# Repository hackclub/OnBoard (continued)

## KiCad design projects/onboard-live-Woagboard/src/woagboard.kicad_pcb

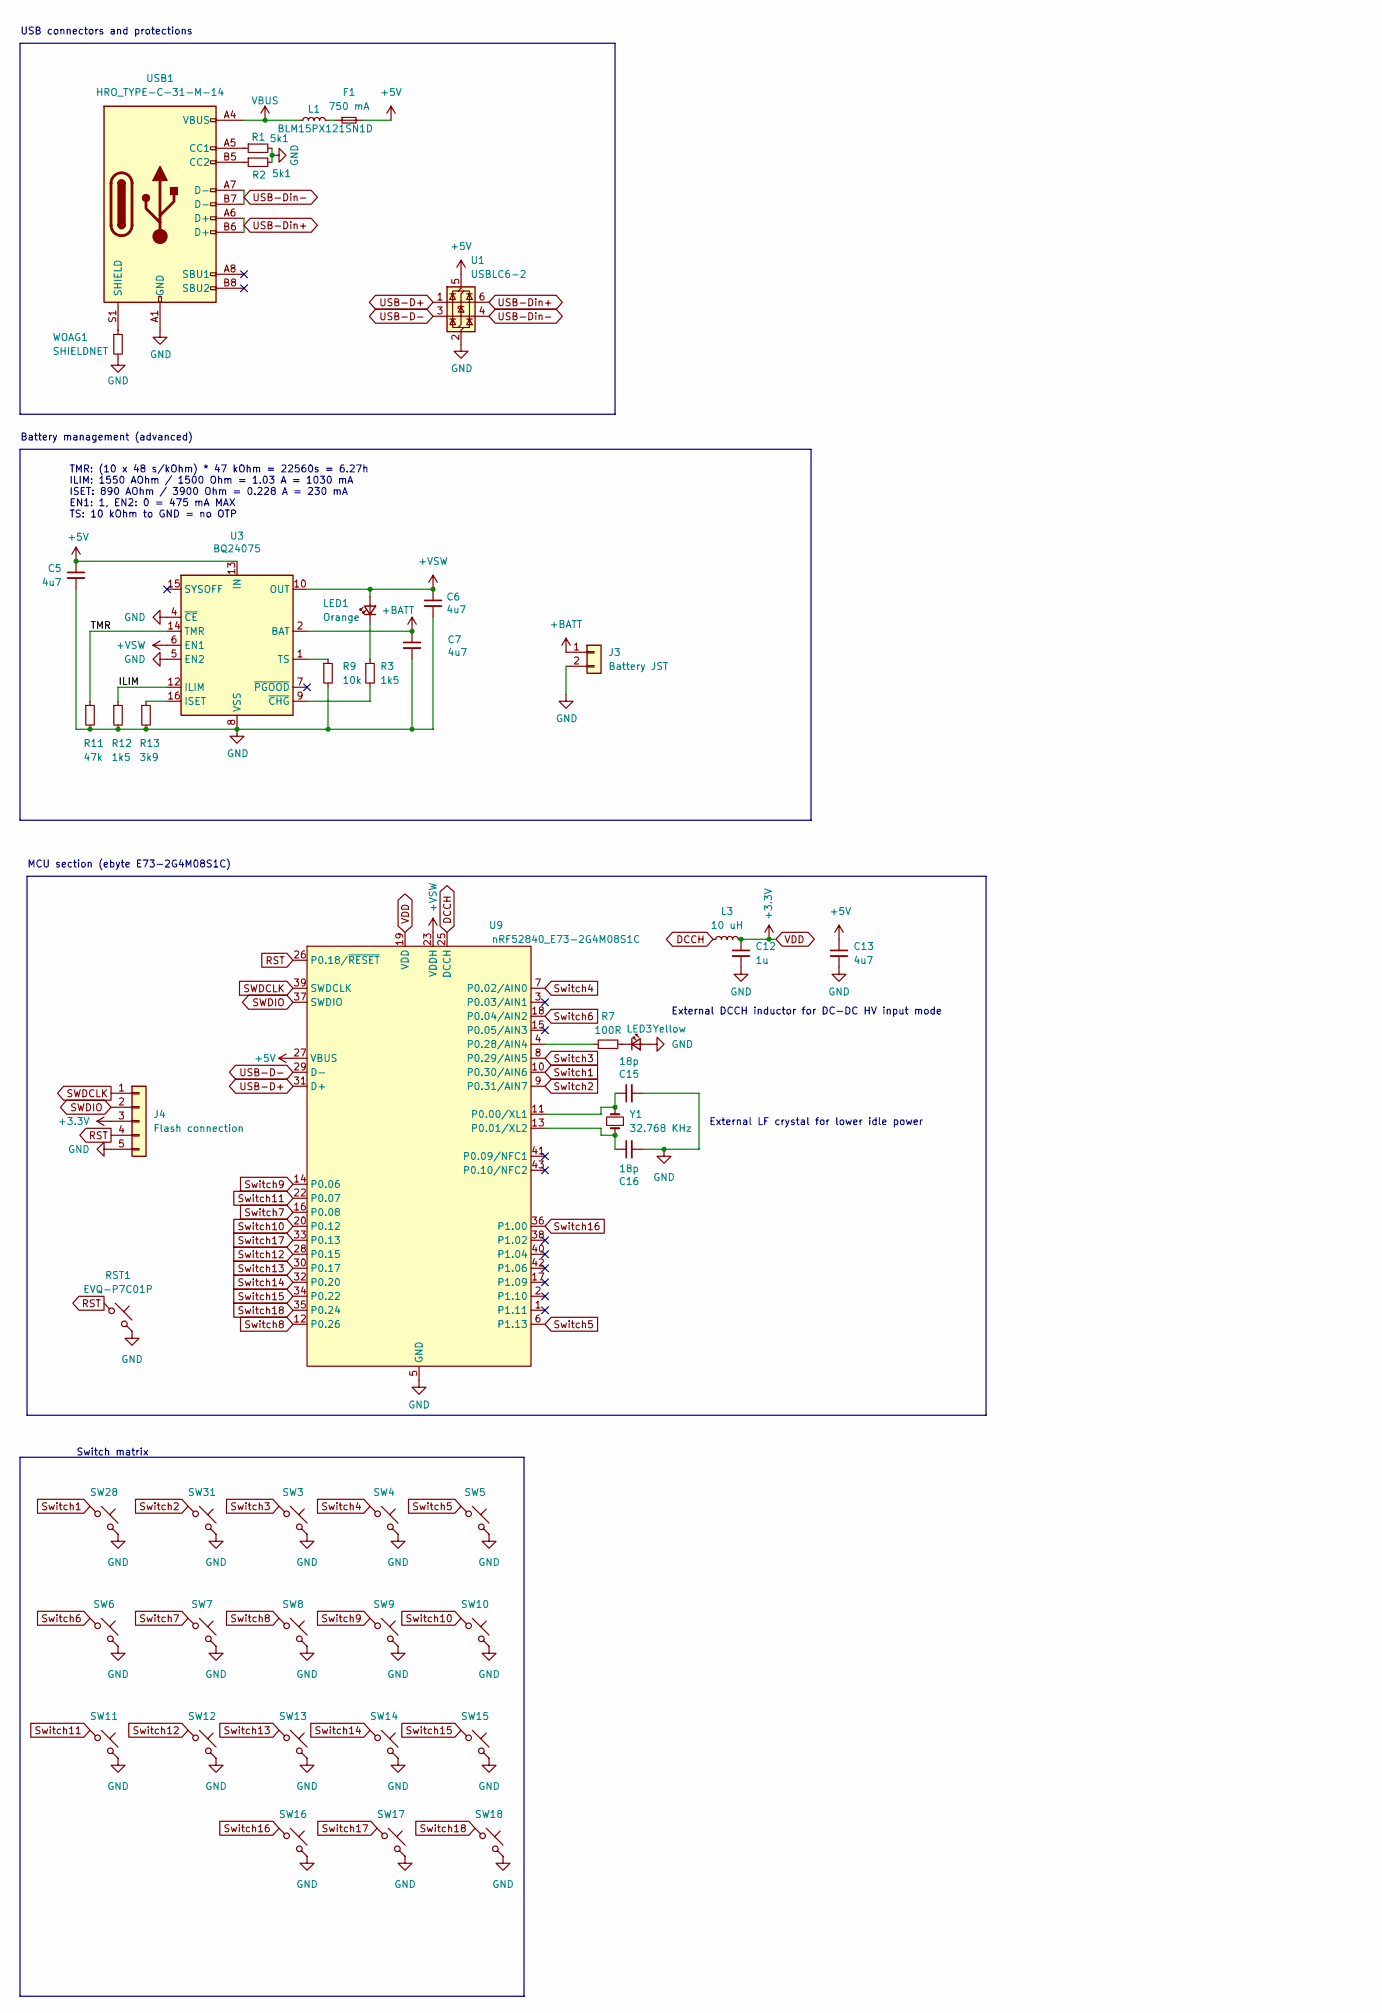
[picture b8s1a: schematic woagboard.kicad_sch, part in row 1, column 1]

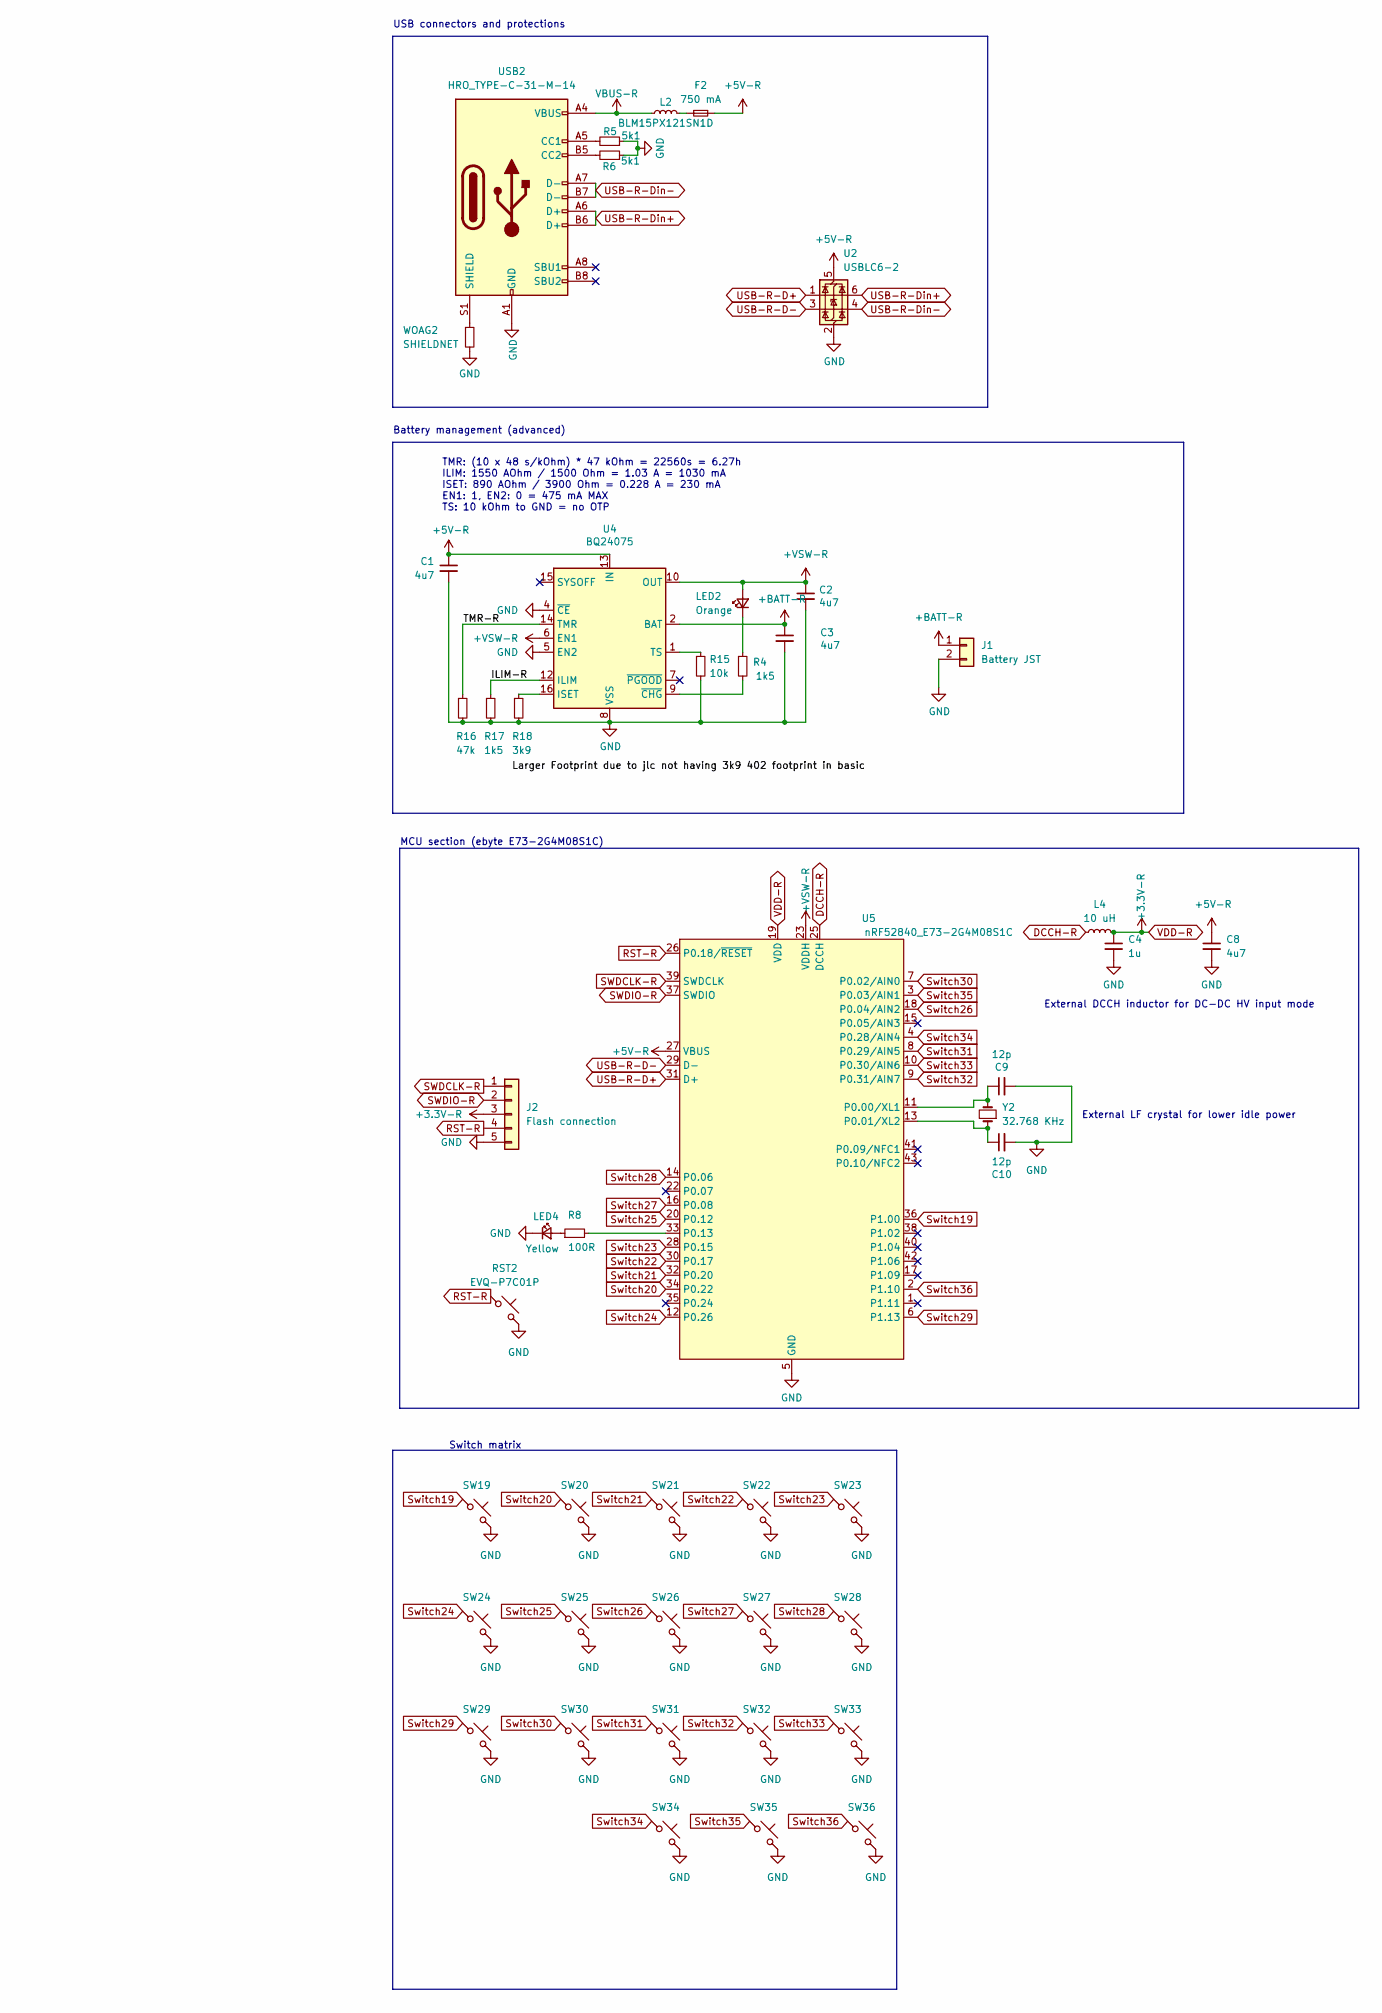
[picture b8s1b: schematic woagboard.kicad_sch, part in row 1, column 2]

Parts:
C1, C2, C3, C5, C6, C7, C8, C13: 4u7; C_0402_1005Metric
C4, C12: 1u; C_0402_1005Metric
C9, C10: 12p; C_0402_1005Metric
C15, C16: 18p; C_0402_1005Metric
F1, F2: 750 mA; Fuse_0603_1608Metric
J1, J3: Battery JST; JST_PH_S2B-PH-K_1x02_P2.00mm_Horizontal
J2, J4: Flash connection; PinHeader_1x05_P2.54mm_Vertical
L1, L2: BLM15PX121SN1D; L_0402_1005Metric
L3, L4: 10 uH; L_0603_1608Metric; LCSC C92982
LED1, LED2: Orange; LED_0805_2012Metric
LED3, LED4: Yellow; LED_0805_2012Metric
R1, R2, R5, R6: 5k1; R_0402_1005Metric
R3, R4, R12, R17: 1k5; R_0402_1005Metric
R7, R8: 100R; R_0402_1005Metric
R9, R15: 10k; R_0402_1005Metric
R11, R16: 47k; R_0402_1005Metric
R13, R18: 3k9; R_0603_1608Metric
RST1, RST2: EVQ-P7C01P; EVQ-P7C
SW3, SW4, SW5, SW6, SW7, SW8, SW9, SW10, SW11, SW12, SW13, SW14, SW15, SW16, SW17, SW18, SW19, SW20, SW21, SW22, SW23, SW24, SW25, SW26, SW27, SW28, SW29, SW30, SW31, SW32, SW33, SW34, SW35, SW36: SW_Push; SW_choc_v1_HS_No_LED
U1, U2: USBLC6-2; SOT-23-6
U3, U4: BQ24075; VQFN-16-1EP_3x3mm_P0.5mm_EP1.68x1.68mm
U5, U9: nRF52840_E73-2G4M08S1C; LCSC C356849
USB1, USB2: HRO_TYPE-C-31-M-14; USB_C_Receptacle_HRO_TYPE-C-31-M-12
WOAG1, WOAG2: SHIELDNET; SolderJumper-2_P1.3mm_Bridged2Bar_RoundedPad1.0x1.5mm
Y1, Y2: 32.768 KHz; Q13FC13500004; LCSC C55208

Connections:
+5V: C5.1, C13.1, F1.2, U1.5 (VBUS), U3.13 (IN), U9.27 (VBUS)
+5V-R: C1.1, C8.1, F2.2, U2.5 (VBUS), U4.13 (IN), U5.27 (VBUS)
+BATT: C7.1, J3.1, U3.2 (BAT), U3.3 (BAT)
+BATT-R: C3.1, J1.1, U4.2 (BAT), U4.3 (BAT)
+VSW: C6.1, LED1.2 (A), U3.6 (EN1), U3.10 (OUT), U3.11 (OUT), U9.23 (VDDH)
+VSW-R: C2.1, LED2.2 (A), U4.6 (EN1), U4.10 (OUT), U4.11 (OUT), U5.23 (VDDH)
/ILIM: R12.1, U3.12 (ILIM)
/ILIM-R: R17.1, U4.12 (ILIM)
/TMR: R11.1, U3.14 (TMR)
/TMR-R: R16.1, U4.14 (TMR)
DCCH: L3.1, U9.25 (DCCH)
DCCH-R: L4.1, U5.25 (DCCH)
GND: C1.2, C2.2, C3.2, C4.2, C5.2, C6.2, C7.2, C8.2, C9.2, C10.2, C12.2, C13.2, C15.2, C16.2, J1.2, J2.5, J3.2, J4.5, LED3.2 (A), LED4.1 (K), R1.2, R2.2, R5.1, R6.1, R9.2, R11.2, R12.2, R13.2, R15.2, R16.2, R17.2, R18.2, RST1.2, RST2.2, SW3.2, SW4.2, SW5.2, SW6.2, SW7.2, SW8.2, SW9.2, SW10.2, SW11.2, SW12.2, SW13.2, SW14.2, SW15.2, SW16.2, SW17.2, SW18.2, SW19.2, SW20.2, SW21.2, SW22.2, SW23.2, SW24.2, SW25.2, SW26.2, SW27.2, SW28.2, SW29.2, SW30.2, SW31.2, SW32.2, SW33.2, SW34.2, SW35.2, SW36.2, U1.2 (GND), U2.2 (GND), U3.4 (~CE), U3.5 (EN2), U3.8 (VSS), U3.17 (VSS), U4.4 (~CE), U4.5 (EN2), U4.8 (VSS), U4.17 (VSS), U5.5 (GND), U5.21 (GND), U5.24 (GND), U9.5 (GND), U9.21 (GND), U9.24 (GND), USB1.A1 (GND), USB1.A12 (GND), USB1.B1 (GND), USB1.B12 (GND), USB2.A1 (GND), USB2.A12 (GND), USB2.B1 (GND), USB2.B12 (GND), WOAG1.2, WOAG2.2; also elsewhere on the board
unnamed: F1.1, L1.2
unnamed: F2.1, L2.2
unnamed: LED1.1 (K), R3.1
unnamed: LED2.1 (K), R4.1
unnamed: LED3.1 (K), R7.2
unnamed: LED4.2 (A), R8.1
unnamed: R13.1, U3.16 (ISET)
unnamed: R9.1, U3.1 (TS)
unnamed: R3.2, U3.9 (~CHG)
unnamed: R18.1, U4.16 (ISET)
unnamed: R15.1, U4.1 (TS)
unnamed: R4.2, U4.9 (~CHG)
unnamed: C9.1, U5.11 (P0.00/XL1), Y2.2
unnamed: C10.1, U5.13 (P0.01/XL2), Y2.1
unnamed: R8.2, U5.33 (P0.13)
unnamed: C15.1, U9.11 (P0.00/XL1), Y1.2
unnamed: C16.1, U9.13 (P0.01/XL2), Y1.1
unnamed: R7.1, U9.4 (P0.28/AIN4)
unnamed: R1.1, USB1.A5 (CC1)
unnamed: R2.1, USB1.B5 (CC2)
unnamed: USB1.S1 (SHIELD), WOAG1.1
unnamed: R5.2, USB2.A5 (CC1)
unnamed: R6.2, USB2.B5 (CC2)
unnamed: USB2.S1 (SHIELD), WOAG2.1
RST: J4.4, RST1.1, U9.26 (P0.18/~RESET)
RST-R: J2.4, RST2.1, U5.26 (P0.18/~RESET)
SWDCLK: J4.1, U9.39 (SWDCLK)
SWDCLK-R: J2.1, U5.39 (SWDCLK)
SWDIO: J4.2, U9.37 (SWDIO)
SWDIO-R: J2.2, U5.37 (SWDIO)
Switch3: SW3.1, U9.8 (P0.29/AIN5)
Switch4: SW4.1, U9.7 (P0.02/AIN0)
Switch5: SW5.1, U9.6 (P1.13)
Switch6: SW6.1, U9.18 (P0.04/AIN2)
Switch7: SW7.1, U9.16 (P0.08)
Switch8: SW8.1, U9.12 (P0.26)
Switch9: SW9.1, U9.14 (P0.06)
Switch10: SW10.1, U9.20 (P0.12)
Switch11: SW11.1, U9.22 (P0.07)
Switch12: SW12.1, U9.28 (P0.15)
Switch13: SW13.1, U9.30 (P0.17)
Switch14: SW14.1, U9.32 (P0.20)
Switch15: SW15.1, U9.34 (P0.22)
Switch16: SW16.1, U9.36 (P1.00)
Switch17: SW17.1, U9.33 (P0.13)
Switch18: SW18.1, U9.35 (P0.24)
Switch19: SW19.1, U5.36 (P1.00)
Switch20: SW20.1, U5.34 (P0.22)
Switch21: SW21.1, U5.32 (P0.20)
Switch22: SW22.1, U5.30 (P0.17)
Switch23: SW23.1, U5.28 (P0.15)
Switch24: SW24.1, U5.12 (P0.26)
Switch25: SW25.1, U5.20 (P0.12)
Switch26: SW26.1, U5.18 (P0.04/AIN2)
Switch27: SW27.1, U5.16 (P0.08)
Switch29: SW29.1, U5.6 (P1.13)
Switch30: SW30.1, U5.7 (P0.02/AIN0)
Switch32: SW32.1, U5.9 (P0.31/AIN7)
Switch33: SW33.1, U5.10 (P0.30/AIN6)
Switch34: SW34.1, U5.4 (P0.28/AIN4)
Switch35: SW35.1, U5.3 (P0.03/AIN1)
Switch36: SW36.1, U5.2 (P1.10)
USB-D+: U1.1 (I/O1), U9.31 (D+)
USB-D-: U1.3 (I/O2), U9.29 (D-)
USB-Din+: U1.6 (I/O1), USB1.A6 (D+), USB1.B6 (D+)
USB-Din-: U1.4 (I/O2), USB1.A7 (D-), USB1.B7 (D-)
USB-R-D+: U2.1 (I/O1), U5.31 (D+)
USB-R-D-: U2.3 (I/O2), U5.29 (D-)
USB-R-Din+: U2.6 (I/O1), USB2.A6 (D+), USB2.B6 (D+)
USB-R-Din-: U2.4 (I/O2), USB2.A7 (D-), USB2.B7 (D-)
VBUS: L1.1, USB1.A4 (VBUS), USB1.A9 (VBUS), USB1.B4 (VBUS), USB1.B9 (VBUS)
VBUS-R: L2.1, USB2.A4 (VBUS), USB2.A9 (VBUS), USB2.B4 (VBUS), USB2.B9 (VBUS)
VDD: C12.1, J4.3, L3.2, U9.19 (VDD)
VDD-R: C4.1, J2.3, L4.2, U5.19 (VDD)

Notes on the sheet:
TMR: (10 x 48 s/kOhm) * 47 kOhm = 22560s = 6.27h ILIM: 1550 AOhm / 1500 Ohm = 1.03 A = 1030 mA ISET: 890 AOhm / 3900 Ohm = 0.228 A = 230 mA EN1: 1, EN2: 0 = 475 mA MAX TS: 10 kOhm to GND = no OTP
Switch matrix
USB connectors and protections
External LF crystal for lower idle power
Battery management (advanced)
External DCCH inductor for DC-DC HV input mode
MCU section (ebyte E73-2G4M08S1C)

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
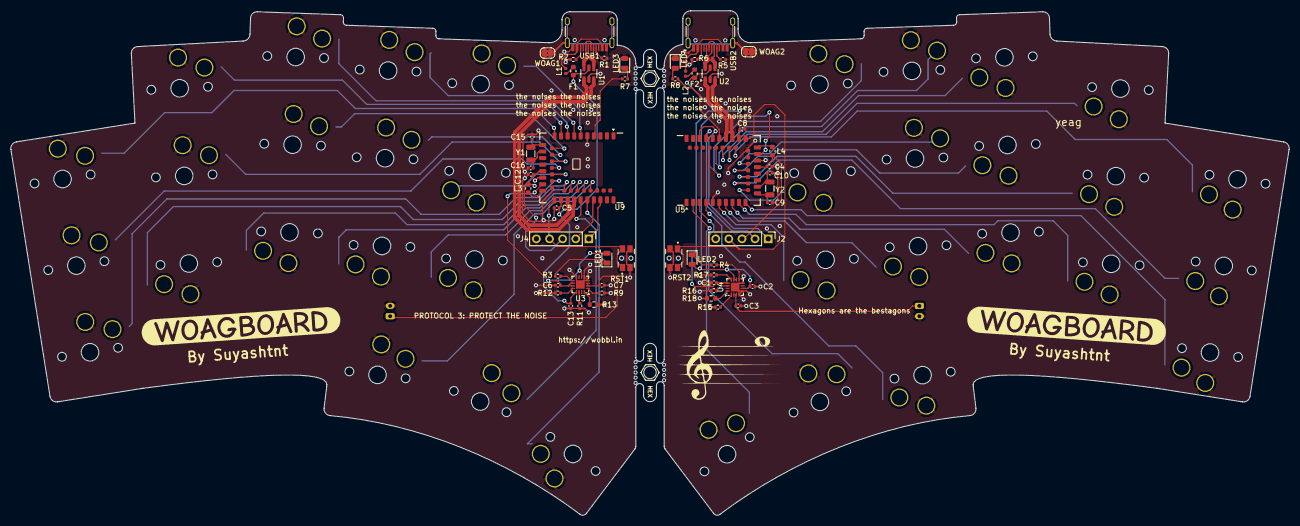
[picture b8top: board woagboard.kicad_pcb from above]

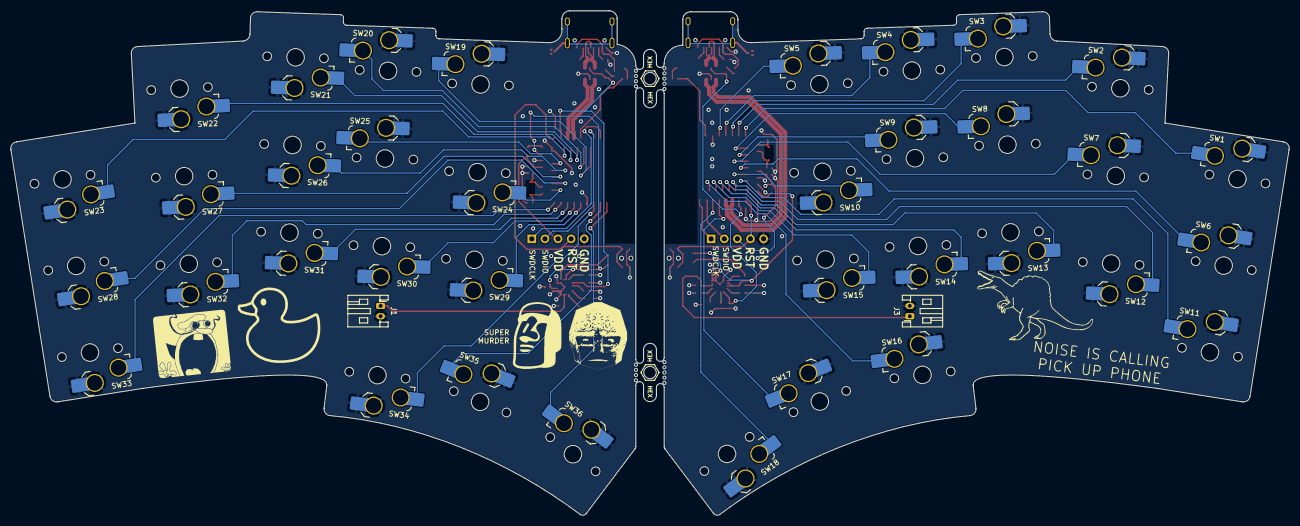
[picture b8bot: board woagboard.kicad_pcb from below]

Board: 2 copper layers, 247.7 x 97.7 mm, 98 parts (38 on the bottom side), 91 nets.

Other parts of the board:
SW1, SW2: SW_Push; SW_choc_v1_HS_No_LED
Snap1, Snap2: 5.5mm; mousebites_5p5mm_easysnap
kibuzzard-66E93FFE, kibuzzard-66E93FFE#2: G***; kibuzzard-66E93FFE

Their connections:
GND: SW1.2, SW2.2; also elsewhere on the board
